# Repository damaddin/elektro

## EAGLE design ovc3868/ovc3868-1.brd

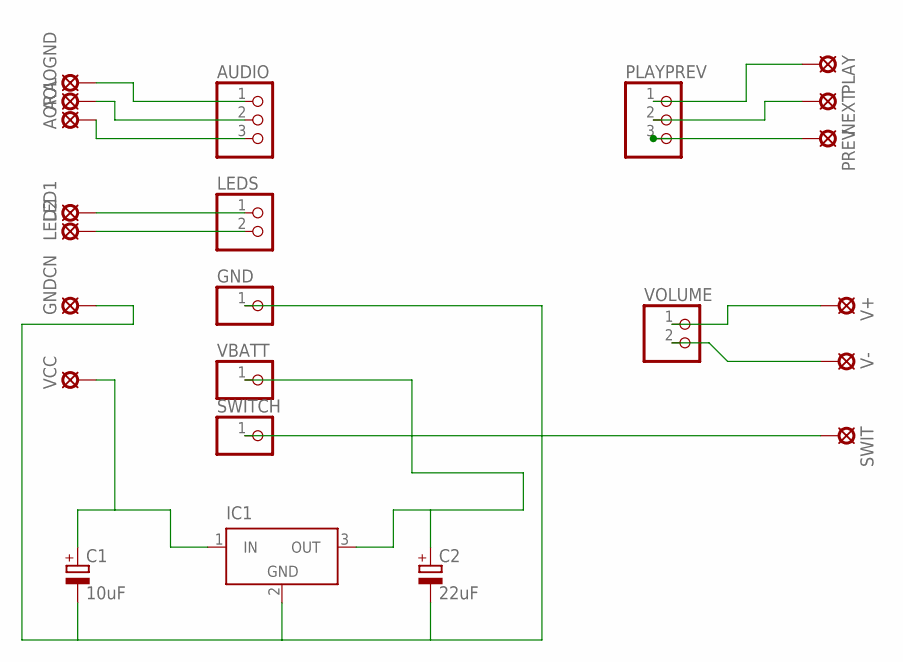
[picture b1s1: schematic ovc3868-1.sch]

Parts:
AOGND: MCS08
AOL: MCS08
AOR: MCS08
AUDIO: PINHD-1X3; 1X03
C1: 10uF; 140CLH-0810
C2: 22uF; 140CLH-0810
GND: PINHD-1X1; 1X01
GNDCN: MCS08
IC1: LT1129CST5; SOT223
LED1, LED2: MCS08
LEDS: PINHD-1X2; 1X02
NEXT: MCS08
PLAY: MCS08
PLAYPREV: PINHD-1X3; 1X03
PREV: MCS08
SWIT: MCS08
SWITCH: PINHD-1X1; 1X01
V+: MCS08
V-: MCS08
VBATT: PINHD-1X1; 1X01
VCC: MCS08
VOLUME: PINHD-1X2; 1X02

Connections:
GND: IC1.4 (GND)
unnamed: C1.+, IC1.1 (IN), VCC.MP
unnamed: C1.-, C2.-, GND.1, GNDCN.MP, IC1.2 (GND)
unnamed: C2.+, IC1.3 (OUT), VBATT.1
unnamed: SWIT.MP, SWITCH.1
unnamed: LED2.MP, LEDS.2
unnamed: LED1.MP, LEDS.1
unnamed: AOR.MP, AUDIO.3
unnamed: AOL.MP, AUDIO.2
unnamed: AOGND.MP, AUDIO.1
unnamed: PLAY.MP, PLAYPREV.1
unnamed: NEXT.MP, PLAYPREV.2
unnamed: PLAYPREV.3, PREV.MP
unnamed: V+.MP, VOLUME.1
unnamed: V-.MP, VOLUME.2

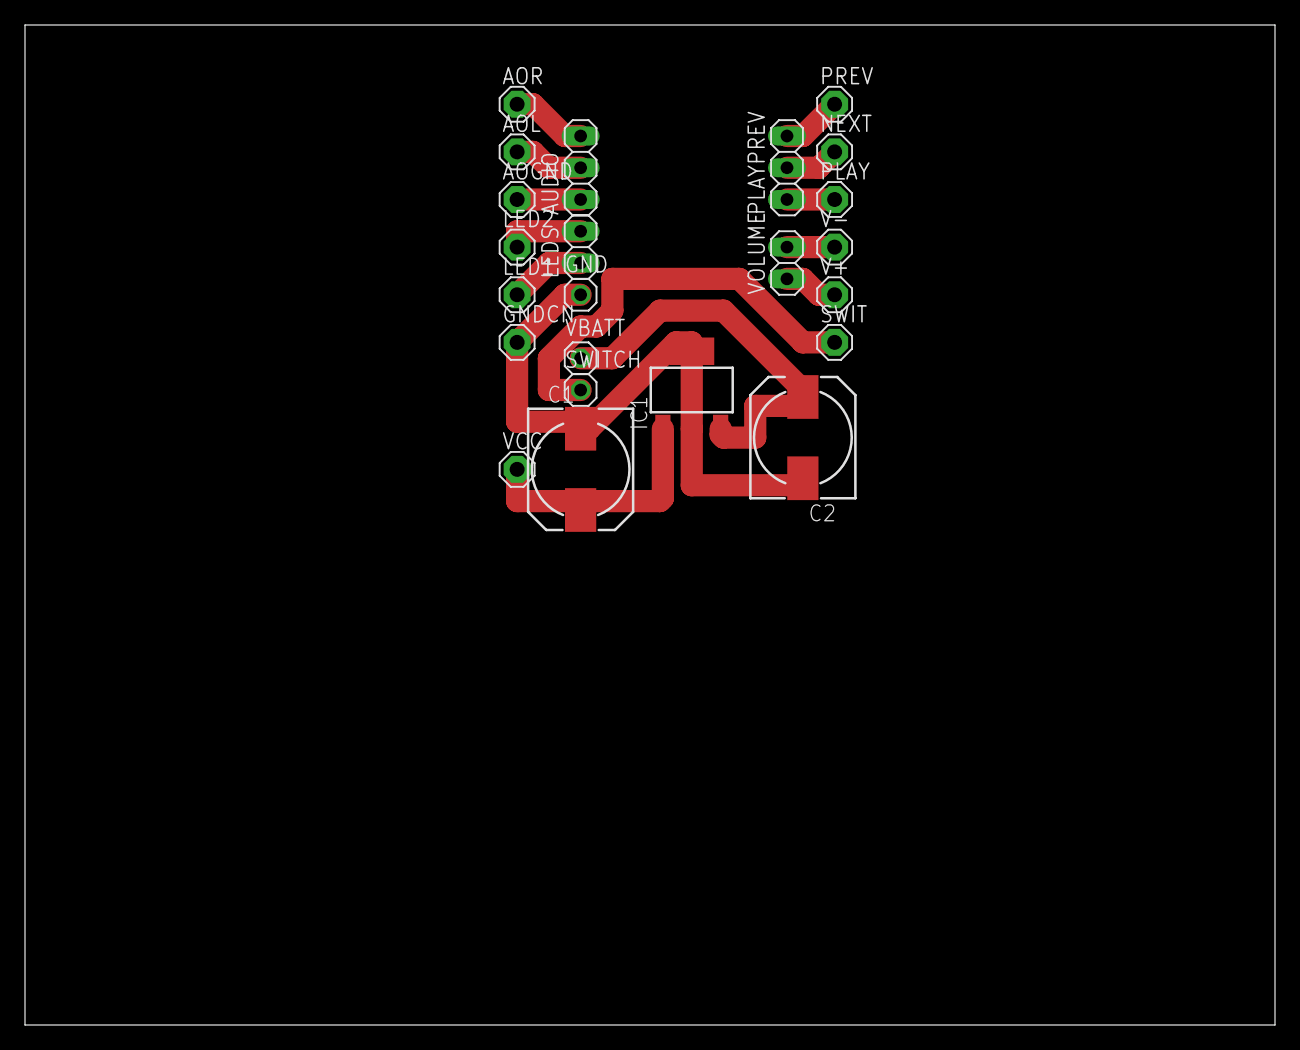
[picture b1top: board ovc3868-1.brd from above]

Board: 2 copper layers, 100.0 x 80.0 mm, 23 parts (0 on the bottom side), 14 nets.

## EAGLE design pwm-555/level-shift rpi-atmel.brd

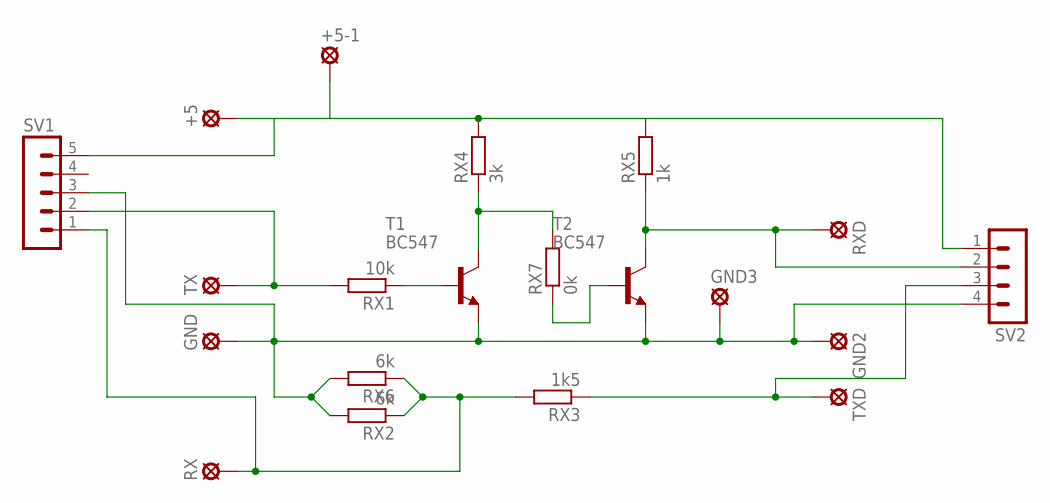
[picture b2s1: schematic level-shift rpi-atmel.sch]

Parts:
+5, +5-1: LSP10
GND, GND2, GND3: LSP10
RX: LSP10
RX1: 10k; 0204/5
RX2, RX6: 6k; 0207/5V
RX3: 1k5; 0207/5V
RX4: 3k; 0207/7
RX5: 1k; 0204/7
RX7: 0k; 0204/5
RXD: LSP10
SV1: MA05-1
SV2: MA04-1
T1, T2: BC547; TO92
TX: LSP10
TXD: LSP10

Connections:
unnamed: RX1.1, T1.2 (B)
unnamed: RX7.1, T2.2 (B)
unnamed: RX5.1, RXD.MP, SV2.2, T2.3 (C)
unnamed: RX4.1, RX7.2, T1.3 (C)
unnamed: GND.MP, GND2.MP, GND3.MP, RX2.2, RX6.2, SV1.3, SV2.4, T1.1 (E), T2.1 (E)
unnamed: RX.MP, RX2.1, RX3.2, RX6.1, SV1.1
unnamed: +5.MP, +5-1.MP, RX4.2, RX5.2, SV1.5, SV2.1
unnamed: RX1.2, SV1.2, TX.MP
unnamed: RX3.1, SV2.3, TXD.MP

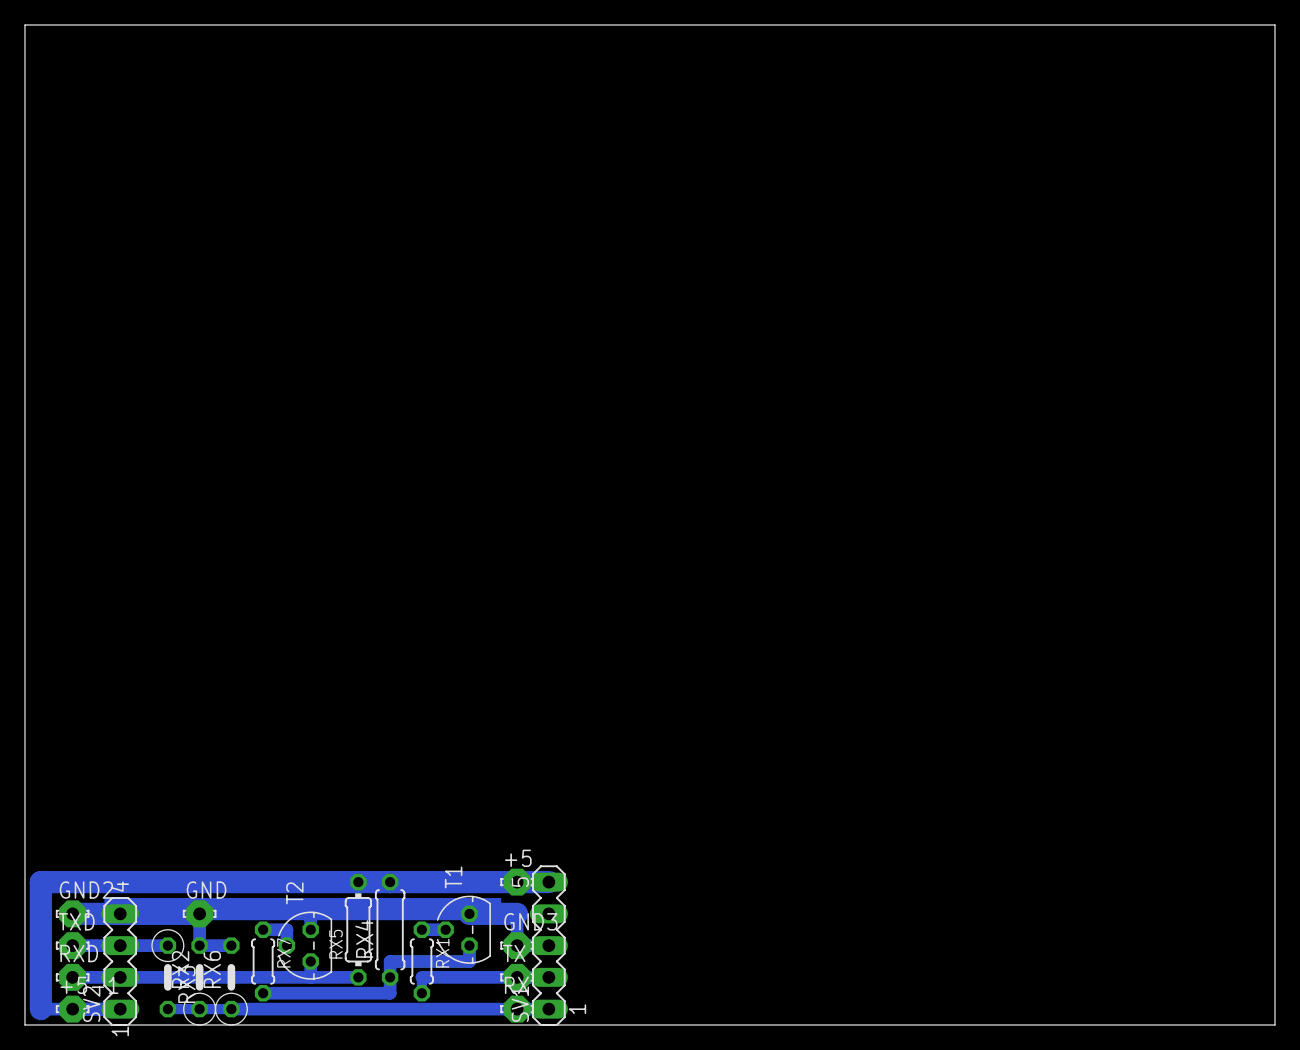
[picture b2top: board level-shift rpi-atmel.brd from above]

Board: 2 copper layers, 100.0 x 80.0 mm, 20 parts (0 on the bottom side), 9 nets.

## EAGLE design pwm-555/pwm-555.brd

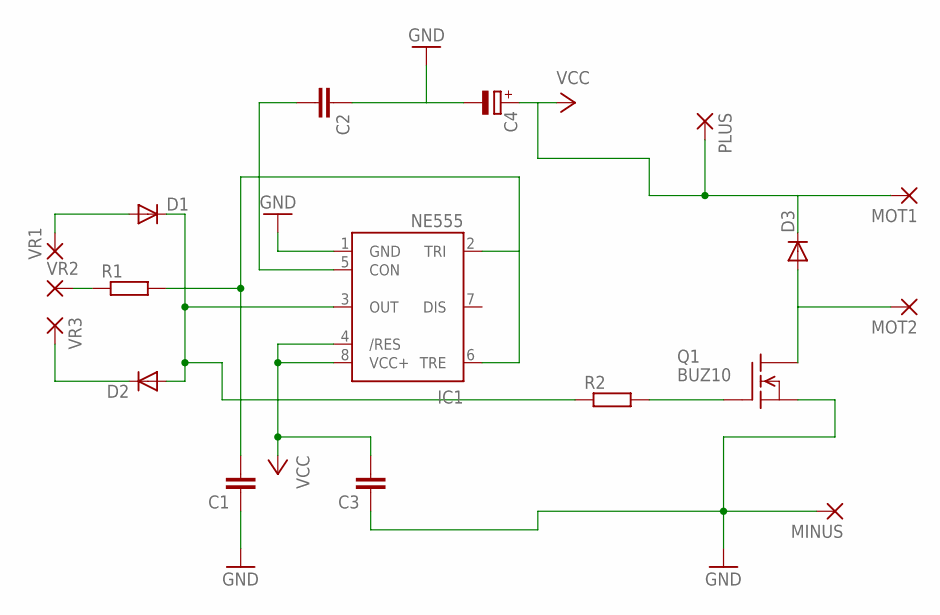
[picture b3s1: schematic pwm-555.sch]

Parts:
C1, C2, C3: C-EU050-030X075; C050-030X075
C4: CPOL-EUE2-5; E2-5
D1, D2, D3: DIODE-D-7.5; D-7.5
IC1: NE555; DIL-08
MINUS: 2,54/0,9
MOT1, MOT2: 2,54/0,9
PLUS: 2,54/0,9
Q1: BUZ10; TO220
R1, R2: R-EU_0204/7; 0204/7
VR1, VR2, VR3: 2,54/0,9

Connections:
GND: C1.1, C2.1, C3.1, C4.-, IC1.1 (GND), MINUS.1, Q1.3 (S)
MOT: D3.A, MOT2.1, Q1.2 (D)
unnamed: D1.A, VR1.1
unnamed: D2.C, VR3.1
unnamed: R1.1, VR2.1
unnamed: C1.2, IC1.2 (TRI), IC1.6 (TRE), R1.2
unnamed: D1.C, D2.A, IC1.3 (OUT), R2.1
unnamed: Q1.1 (G), R2.2
unnamed: C2.2, IC1.5 (CON)
VCC: C3.2, C4.+, D3.C, IC1.4 (/RES), IC1.8 (VCC+), MOT1.1, PLUS.1

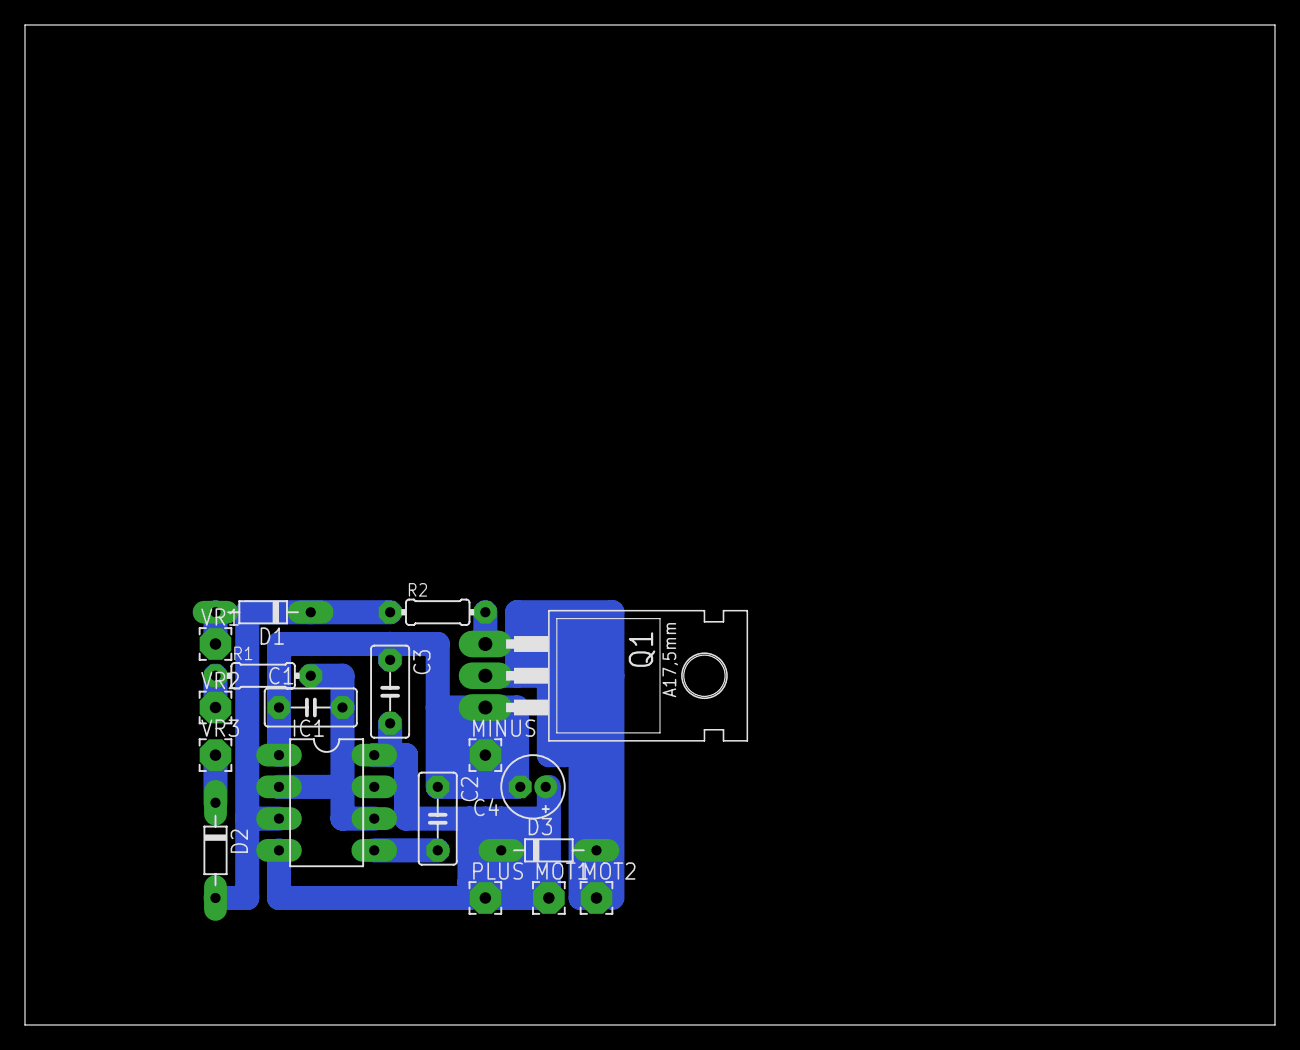
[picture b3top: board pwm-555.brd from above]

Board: 2 copper layers, 100.0 x 80.0 mm, 18 parts (0 on the bottom side), 10 nets.

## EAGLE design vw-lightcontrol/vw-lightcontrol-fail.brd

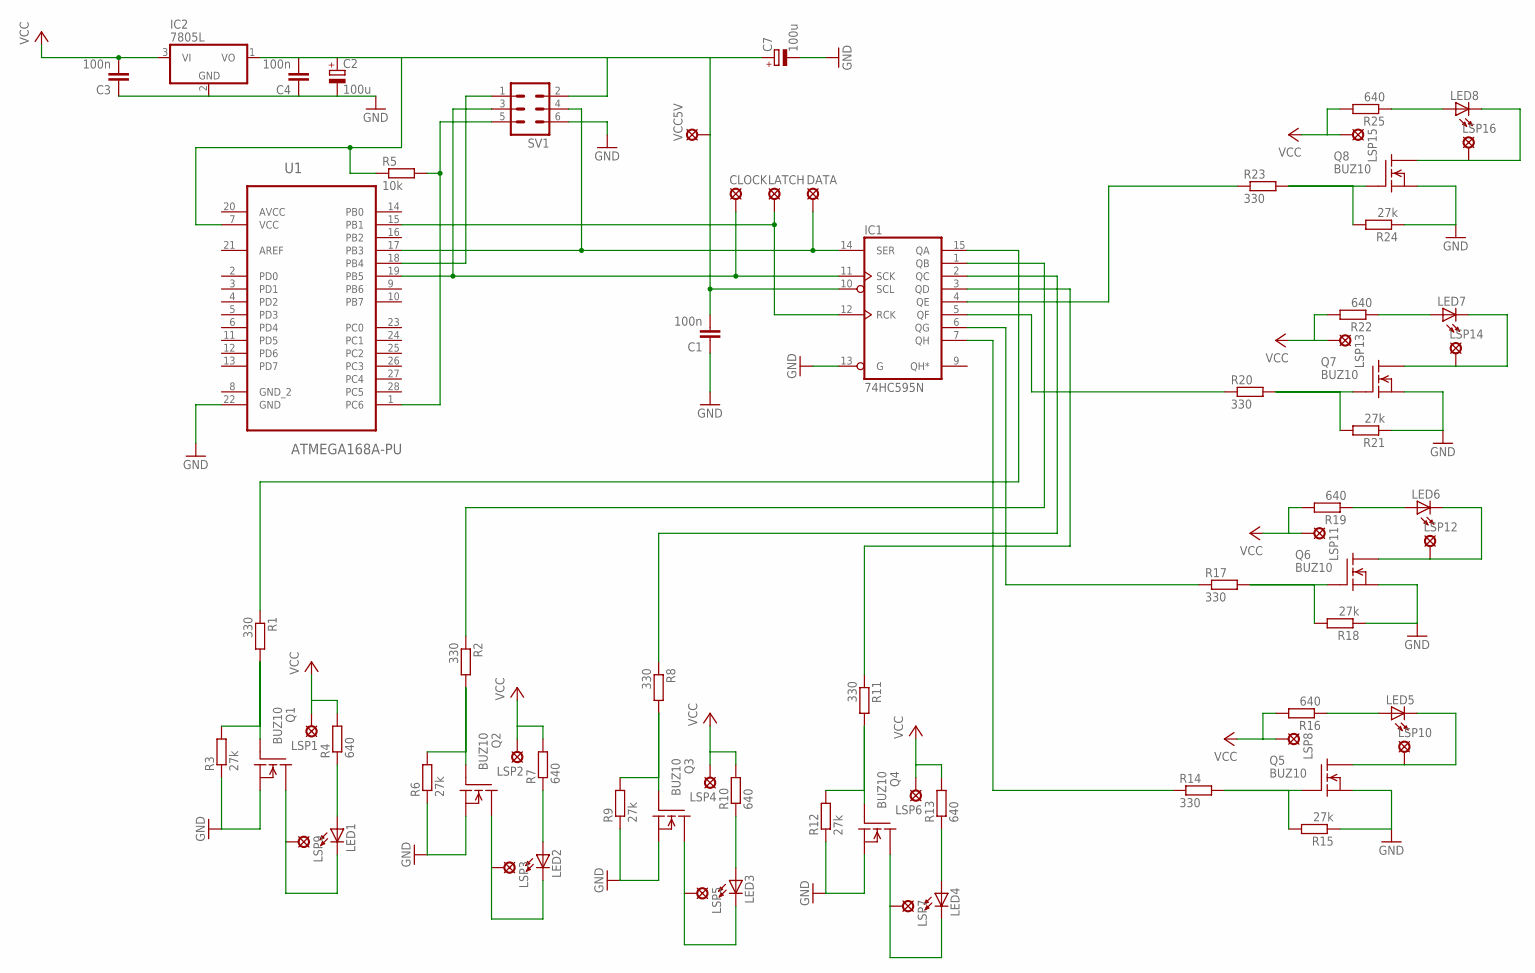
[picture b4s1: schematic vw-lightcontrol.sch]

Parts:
C1, C3, C4: 100n; C2.5-4
C2, C7: 100u; E2,5-6E
CLOCK: LSP10
DATA: LSP10
IC1: 74HC595N; DIL16
IC2: 7805L; TO92
LATCH: LSP10
LED1, LED2, LED3, LED4, LED5, LED6, LED7, LED8: LED3MM
LSP1, LSP2, LSP3, LSP4, LSP5, LSP6, LSP7, LSP8, LSP9, LSP10, LSP11, LSP12, LSP13, LSP14, LSP15, LSP16: LSP10
Q1, Q2, Q3, Q4, Q5, Q6, Q7, Q8: BUZ10; TO220
R1, R2, R8, R11, R14, R17, R20, R23: 330; 0207/10
R3, R6, R9, R12, R15, R18, R21, R24: 27k; 0207/10
R4, R7, R10, R13, R16, R19, R22, R25: 640; 0207/10
R5: 10k; 0207/10
SV1: MA03-2
U1: ATMEGA168A-PU; DIP254P762X457-28
VCC5V: LSP10

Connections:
AVCC: U1.20 (AVCC)
GND: C2.-, C3.1, C4.1, IC1.13 (G), IC2.2 (GND), Q1.3 (S), Q2.3 (S), Q3.3 (S), Q4.3 (S), Q5.3 (S), Q6.3 (S), Q7.3 (S), Q8.3 (S), R3.1, R6.1, R9.1, R12.1, R15.1, R18.1, R21.1, R24.1, SV1.6, U1.22 (GND)
unnamed: LED1.A, R4.1
unnamed: Q1.1 (G), R1.2, R3.2
unnamed: LED1.K (C), LSP9.MP, Q1.2 (D)
unnamed: IC1.15 (QA), R1.1
unnamed: LED2.A, R7.1
unnamed: Q2.1 (G), R2.2, R6.2
unnamed: LED2.K (C), LSP3.MP, Q2.2 (D)
unnamed: IC1.1 (QB), R2.1
unnamed: LED3.A, R10.1
unnamed: Q3.1 (G), R8.2, R9.2
unnamed: LED3.K (C), LSP5.MP, Q3.2 (D)
unnamed: IC1.2 (QC), R8.1
unnamed: LED4.A, R13.1
unnamed: Q4.1 (G), R11.2, R12.2
unnamed: LED4.K (C), LSP7.MP, Q4.2 (D)
unnamed: IC1.3 (QD), R11.1
unnamed: LED5.A, R16.1
unnamed: R5.2, SV1.5, U1.1 (PC6)
unnamed: Q5.1 (G), R14.2, R15.2
unnamed: DATA.MP, IC1.14 (SER), SV1.4, U1.17 (PB3)
unnamed: SV1.1, U1.18 (PB4)
unnamed: LED5.K (C), LSP10.MP, Q5.2 (D)
unnamed: IC1.7 (QH), R14.1
unnamed: LED6.A, R19.1
unnamed: Q6.1 (G), R17.2, R18.2
unnamed: LED6.K (C), LSP12.MP, Q6.2 (D)
unnamed: IC1.6 (QG), R17.1
unnamed: LED7.A, R22.1
unnamed: Q7.1 (G), R20.2, R21.2
unnamed: LED7.K (C), LSP14.MP, Q7.2 (D)
unnamed: IC1.5 (QF), R20.1
unnamed: LED8.A, R25.1
unnamed: Q8.1 (G), R23.2, R24.2
unnamed: LED8.K (C), LSP16.MP, Q8.2 (D)
unnamed: IC1.4 (QE), R23.1
unnamed: CLOCK.MP, IC1.11 (SCK), SV1.3, U1.19 (PB5)
unnamed: C1.1, C7.-, IC1.8 (GND)
unnamed: IC1.12 (RCK), LATCH.MP, U1.15 (PB1)

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
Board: 2 copper layers, 70 parts (0 on the bottom side), 41 nets, no tracks yet.
